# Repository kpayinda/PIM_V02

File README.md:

# PIM_V02
Flight-like design of PIM. After dev PIM_V01 was proven, this adds an FPGA and optimises size.

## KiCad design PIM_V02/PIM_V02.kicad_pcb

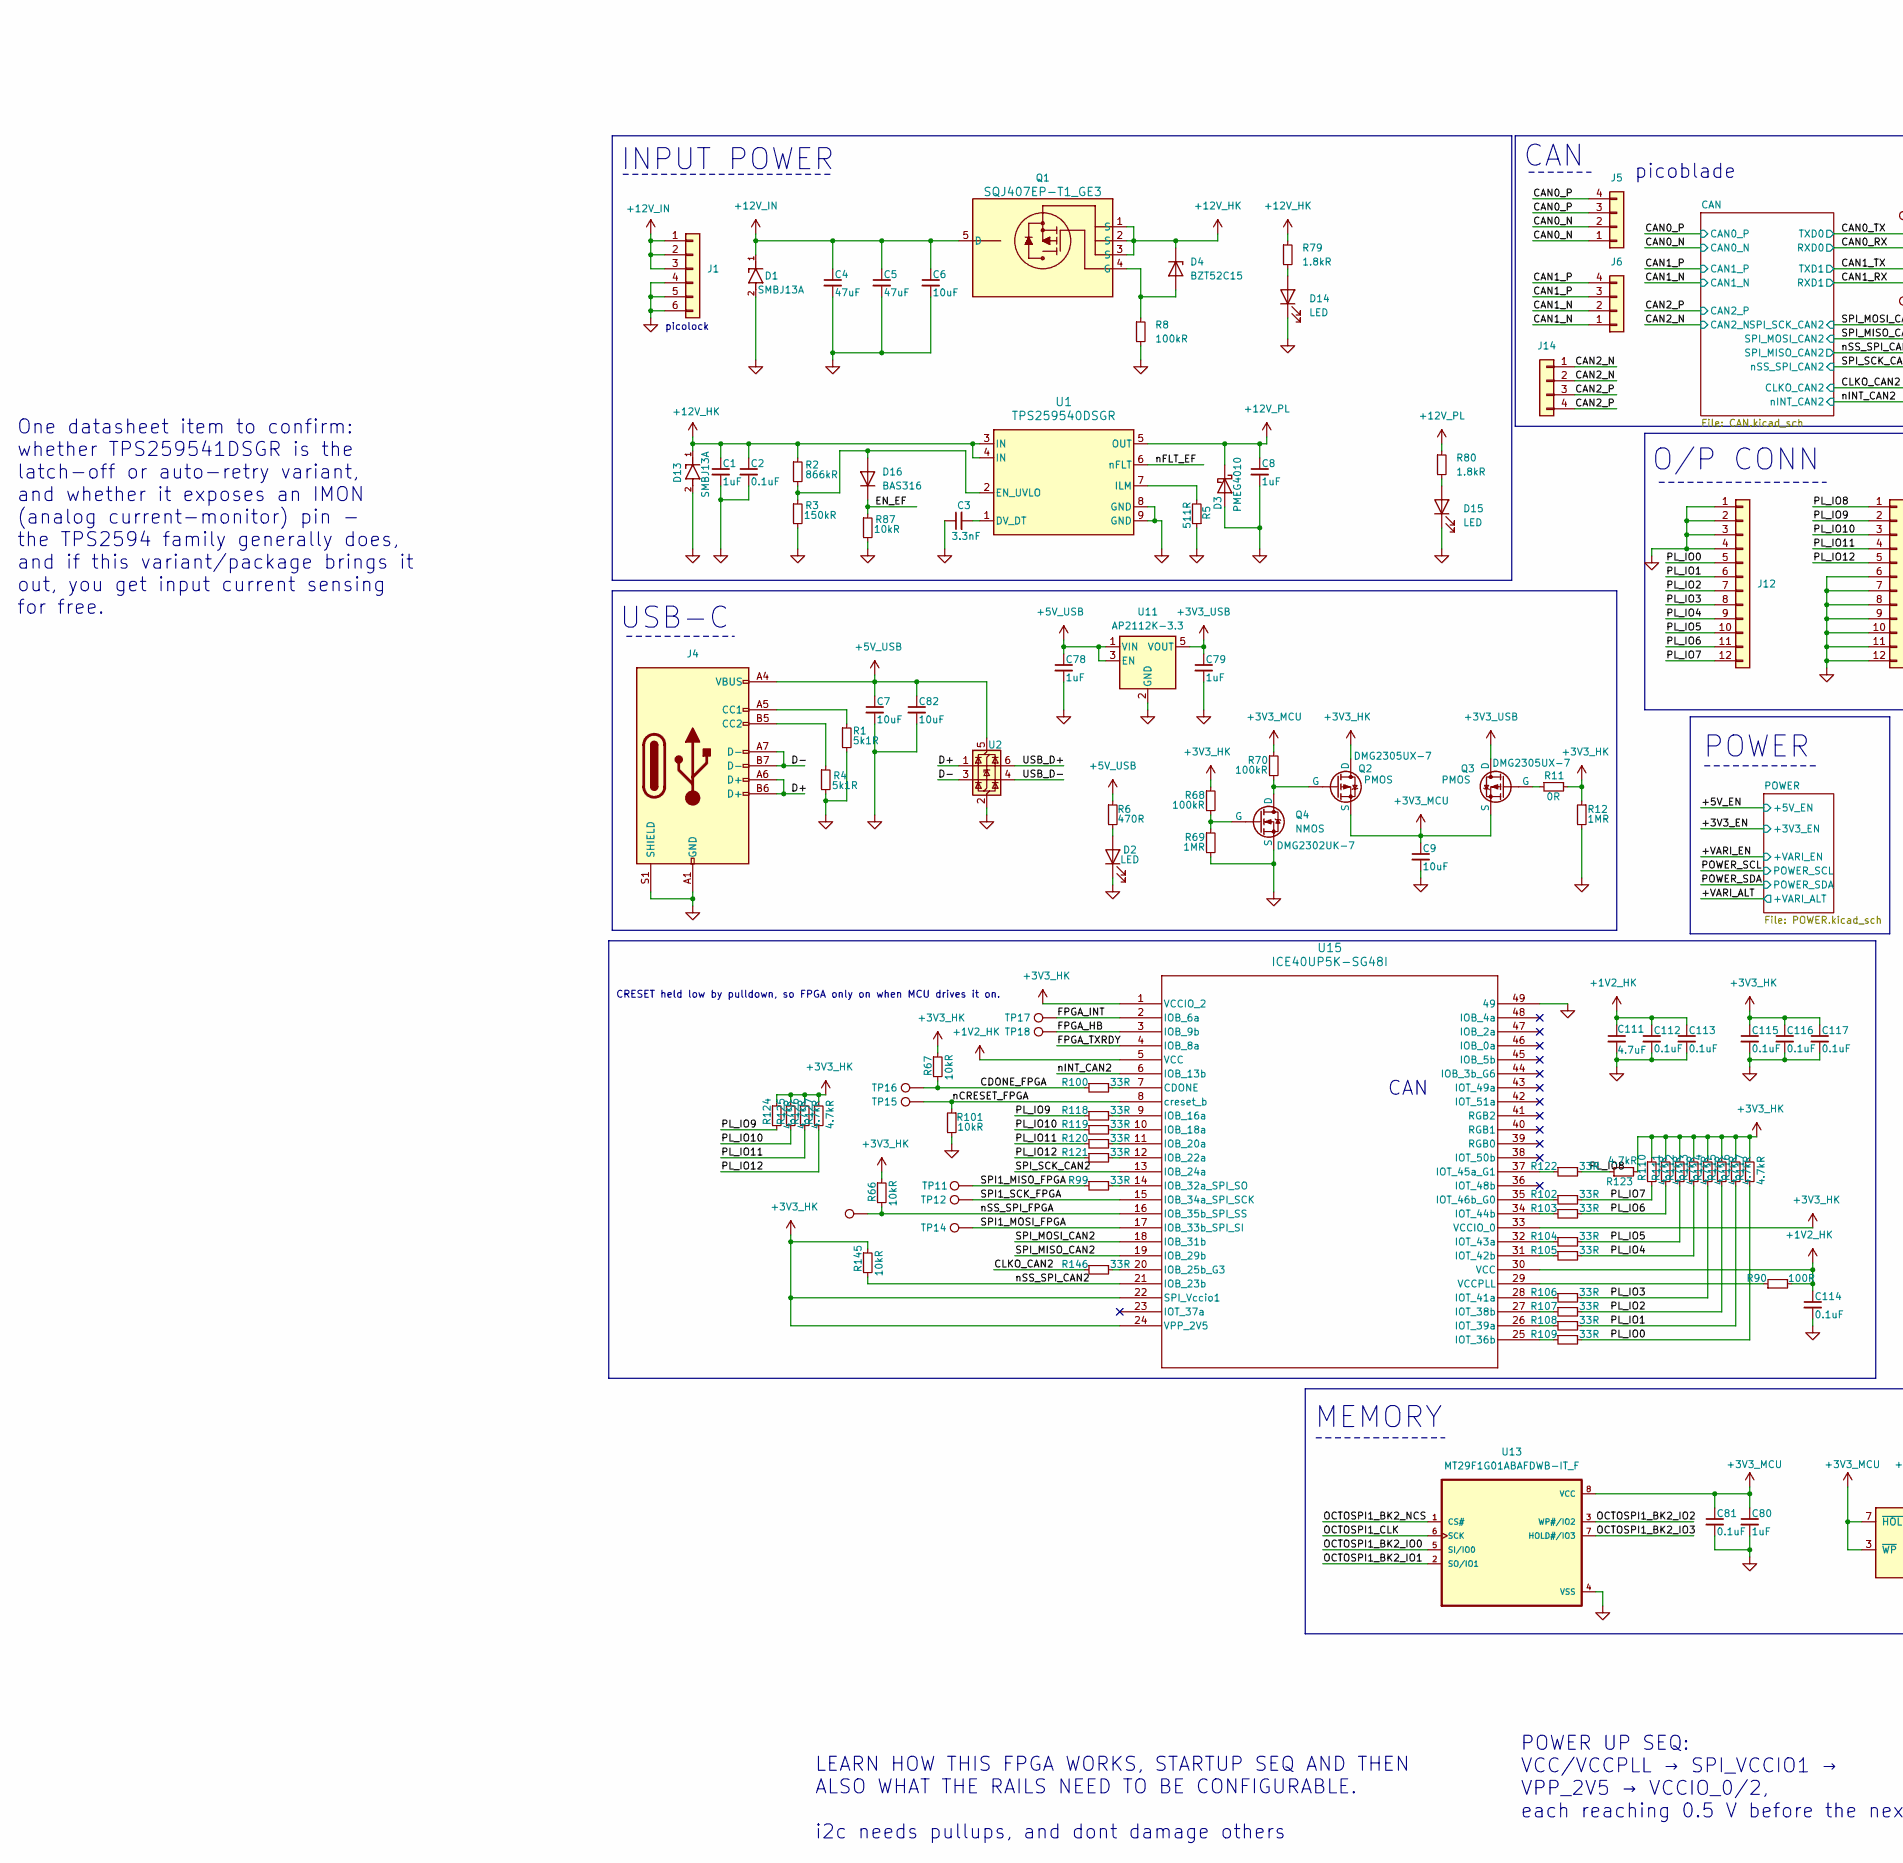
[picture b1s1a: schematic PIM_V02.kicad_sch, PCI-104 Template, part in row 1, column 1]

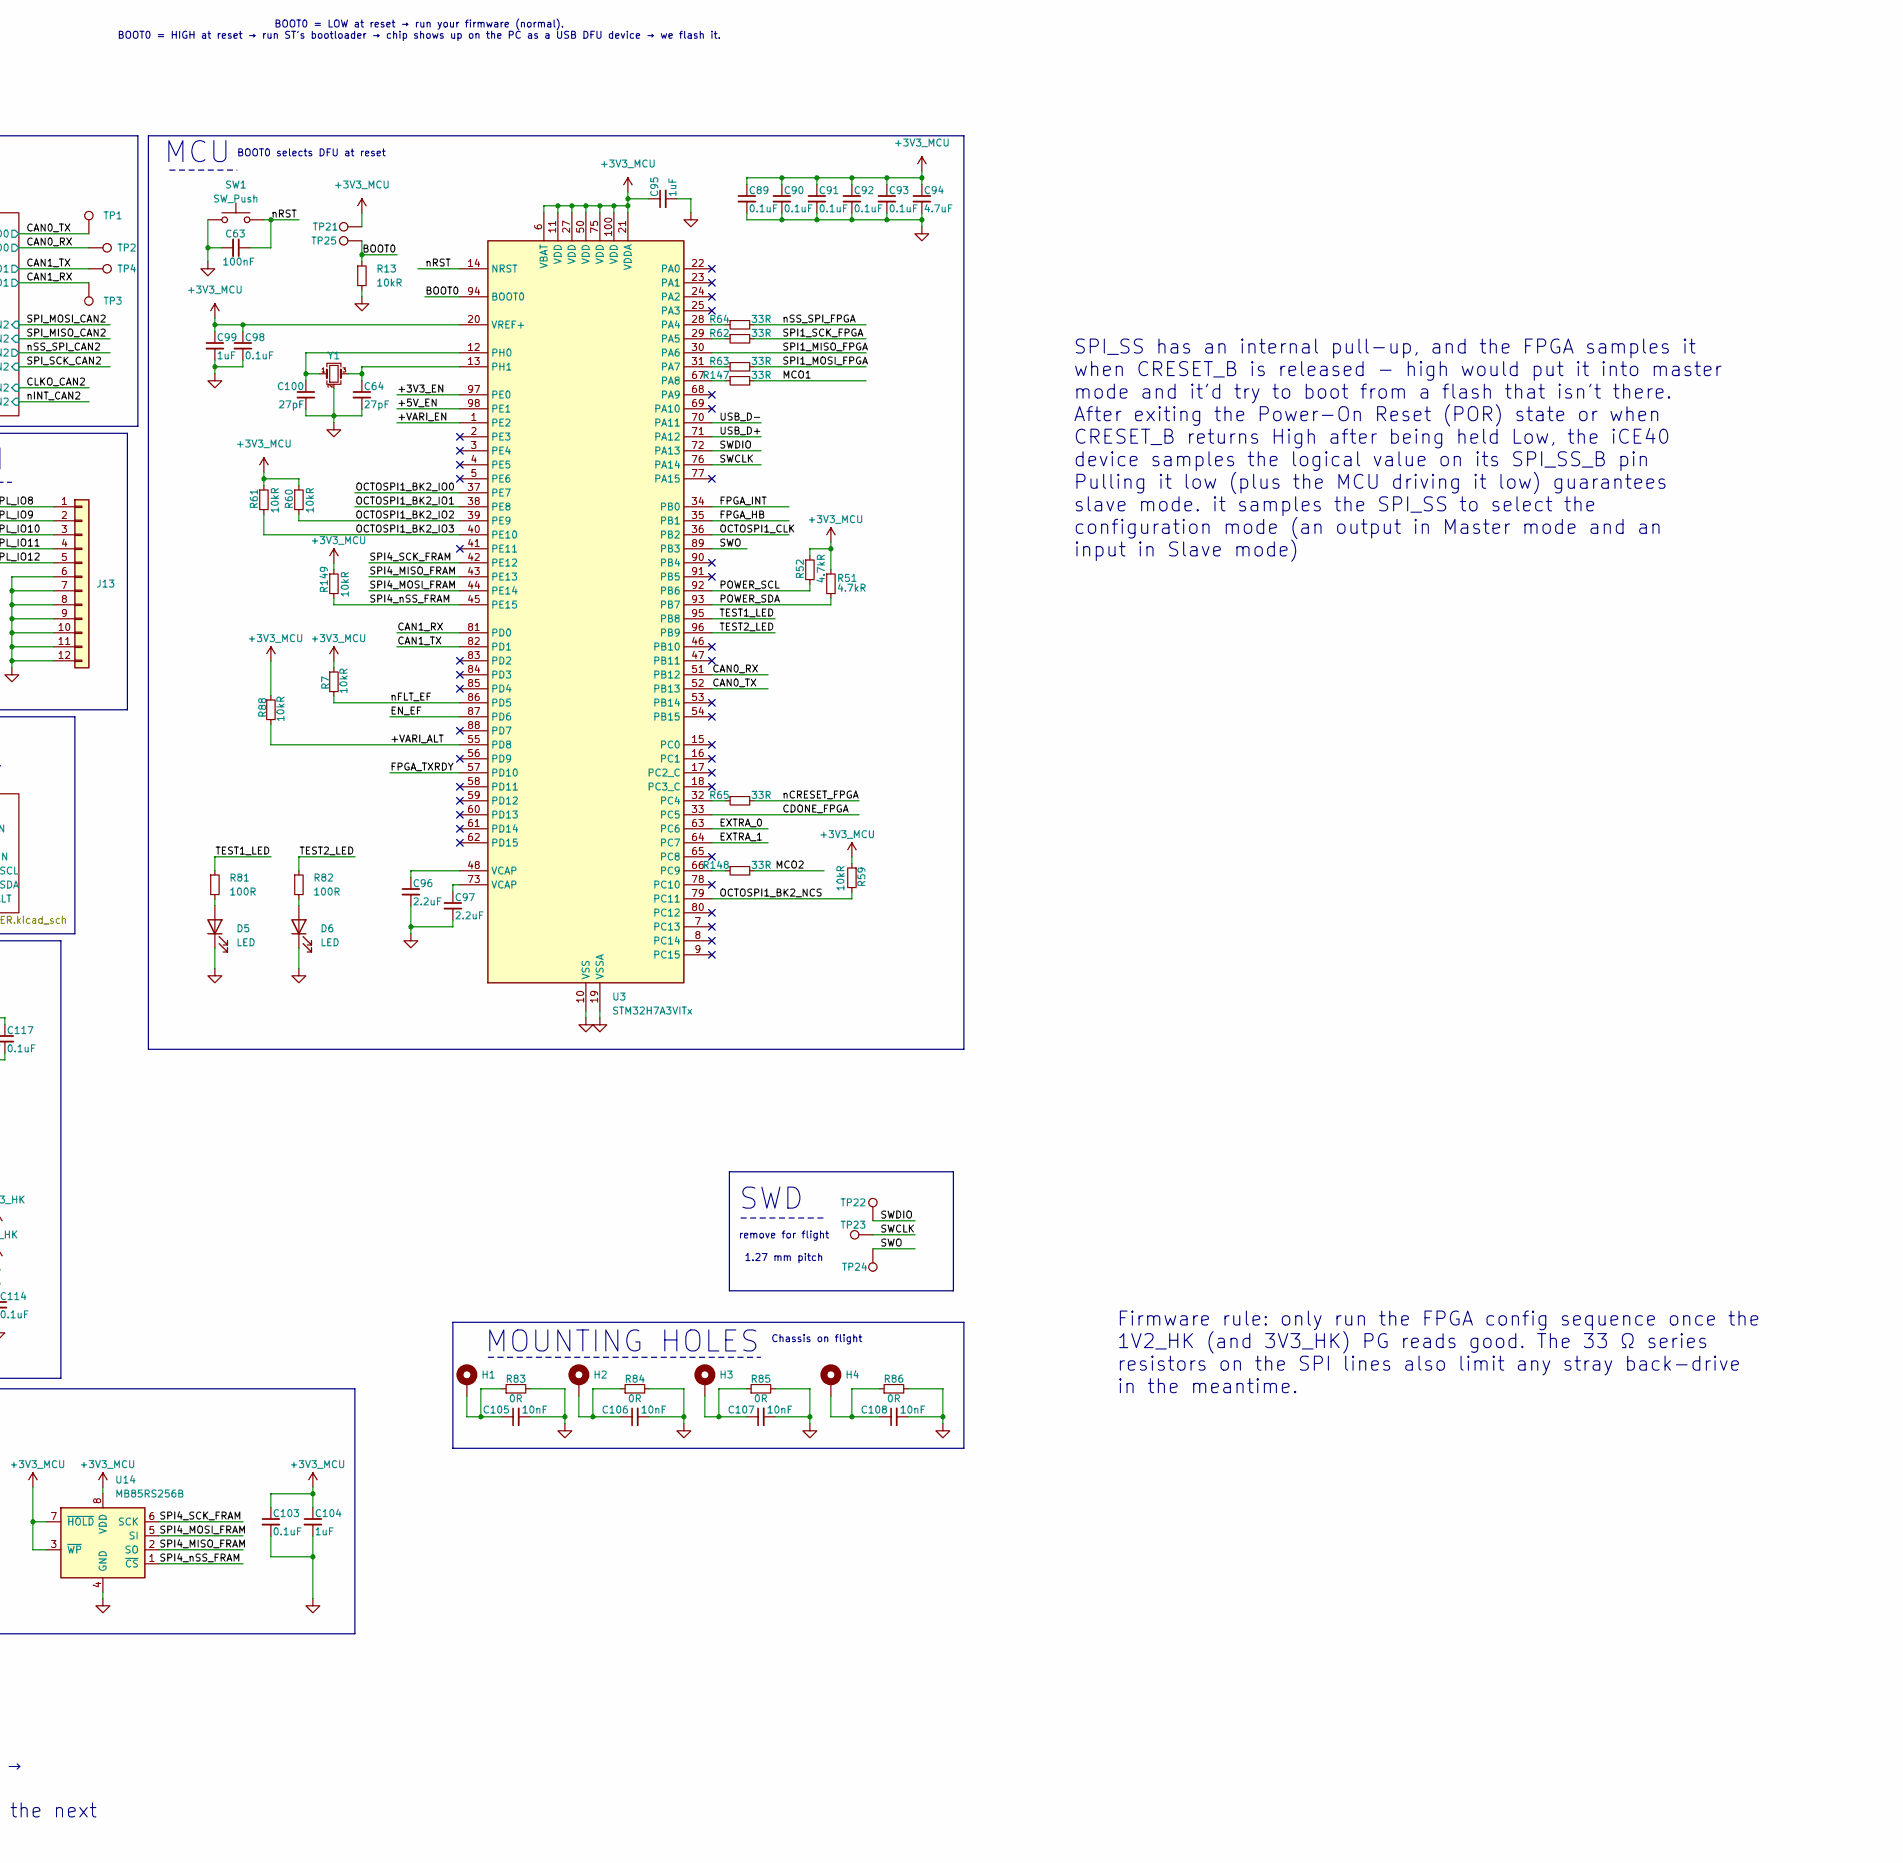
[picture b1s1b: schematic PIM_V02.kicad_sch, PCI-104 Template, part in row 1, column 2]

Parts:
C1, C8, C78, C79, C80, C95, C99, C104: 1uF; C_0603_1608Metric; MPN GCM188R71E105KA64J
C2, C81, C89, C90, C91, C92, C93, C98, C103, C112, C113, C114, C115, C116, C117: 0.1uF; C_0603_1608Metric; MPN GCM188R71H104KA57D
C3: 3.3nF; C_0603_1608Metric; MPN GCM1885C1H332JA16D
C4, C5: 47uF; C_1206_3216Metric; Rating 50V, MLCC; MPN GMC31X5R476M25NT
C6, C7, C9, C82: 10uF; C_0603_1608Metric; MPN GRT188R61E106ME13D
C63: 100nF; C_0603_1608Metric; MPN GCM188R71H104KA57D
C64, C100: 27pF; C_0603_1608Metric; MPN GCM1885C1H270JA16D
C94, C111: 4.7uF; C_0603_1608Metric; MPN MSAST168BB5475MTNA01
C96, C97: 2.2uF; C_0603_1608Metric; MPN GRT188R61E225ME13D
C105, C106, C107, C108: 10nF; C_0603_1608Metric; MPN GCM188R71H103KA37J
D1, D13: SMBJ13A
D2, D5, D6, D14, D15: LED; LED_0603_1608Metric; MPN 150060GS75000
D3: PMEG4010; Nexperia_CFP3_SOD-123W; MPN PMEG4010ER,115
D4: BZT52C15; Nexperia_CFP3_SOD-123W; MPN BZT52C15
D16: BAS316; D_SOD-323
H1, H2, H3, H4: MountingHole_Pad; MountingHole_2.2mm_M2_Pad
J1: Conn_01x06; Molex_Pico-Lock_504050-0691_1x06-1MP_P1.50mm_Horizontal; MPN 5040500691
J4: USB_C_Receptacle_USB2.0_14P; USB_C_Receptacle_GCT_USB4105-xx-A_16P_TopMnt_Horizontal; MPN USB4105-GF-A
J5, J6, J14: Conn_01x04; Molex_PicoBlade_53261-0471_1x04-1MP_P1.25mm_Horizontal; MPN 0532610471
J12, J13: Conn_01x12; 5040501291
Q1: SQJ407EP-T1_GE3; PowerPAK-SO-8L_Option-2_VIS; MPN SQJ407EP-T1_GE3
Q2, Q3: PMOS; SOT-23-3; MPN DMG2305UX-7
Q4: NMOS; SOT-23-3; MPN DMG2302UK-7
R1, R4: 5k1R; R_0603_1608Metric; MPN ERJ-3EKF5101V
R2: 866kR; R_0603_1608Metric; MPN ERJ-3EKF8663V
R3: 150kR; R_0603_1608Metric; MPN ERJ-3EKF1503V
R5: 511R; R_0603_1608Metric; MPN ERJ-3EKF5110V
R6: 470R; R_0603_1608Metric; MPN ERJ-3EKF4700V
R7, R13, R59, R60, R61, R66, R67, R88, R145, R149: 10kR; R_0603_1608Metric; MPN ERJ-3EKF1002V
R8, R68, R70: 100kR; R_0603_1608Metric; MPN ERJ-3EKF1003V
R11, R83, R84, R85, R86: 0R; R_0603_1608Metric; MPN ERJ-3GEY0R00V
R12, R69: 1MR; R_0603_1608Metric; MPN ERJ-3EKF1004V
R51, R52: 4.7kR; R_0603_1608Metric; MPN ERJ-3EKF4701V
R62, R63, R64, R65, R122, R147, R148: 33R; R_0603_1608Metric; MPN ERJ-3EKF33R0V
R79, R80: 1.8kR; R_0603_1608Metric; MPN ERJ-3EKF1801V
R81, R82, R90: 100R; R_0603_1608Metric; MPN ERJ-3EKF1000V
R87, R101: 10kR; R_0603_1608Metric
R99, R100, R102, R103, R104, R105, R106, R107, R108, R109, R118, R119, R120, R121, R146: 33R; R_0402_1005Metric; MPN ERJ-2RKF33R0X
R110, R111, R112, R113, R114, R115, R116, R117, R123, R124, R125, R126, R127: 4.7kR; R_0402_1005Metric; MPN ERJ-2RKF4701X
SW1: SW_Push; SW_SPST_B3U-1000P; MPN B3U-1000P
TP1, TP2, TP3, TP4, TP11, TP12, TP13, TP14, TP15, TP16, TP17, TP18, TP21, TP22, TP23, TP24, TP25: TestPoint; TestPoint_Pad_D1.0mm
U1: TPS259540DSGR; DSG0008A; MPN TPS259540DSGR
U2: USBLC6-2SC6; SOT-23-6; MPN USBLC6-2SC6
U3: STM32H7A3VITx; LQFP-100_14x14mm_P0.5mm; MPN STM32H7A3VIT6
U11: AP2112K-3.3; SOT-23-5; MPN AP2112K-3.3TRG1
U13: MT29F1G01ABAFDWB-IT_F; GD5F1GQ5UEYIGR; PARTREV LTR
U14: MB85RS256B; JEITA_SOIC-8_3.9x4.9mm_P1.27mm; MPN MB85RS256BPNF-G-AMERE2
U15: ICE40UP5K-SG48I; QFN48_L-ASC10_ICE40ULTRAPLUS_MACHXO2_LAT
Y1: Crystal_GND24_Small; Crystal_SMD_Abracon_ABM8G-4Pin_3.2x2.5mm; MPN ABM8G-24.000MHZ-18-D2Y-T3

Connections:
+1V2_HK: C111.1, C112.1, C113.1, C114.1, R90.2, U15.5 (VCC), U15.30 (VCC); also elsewhere on the board
+3V3_HK: C115.1, C116.1, C117.1, Q2.1 (D), R11.2, R12.1, R66.1, R67.1, R68.1, R110.1, R111.1, R112.1, R113.1, R114.1, R115.1, R116.1, R117.1, R123.2, R124.1, R125.1, R126.1, R127.1, R145.1, U15.1 (VCCIO_2), U15.22 (SPI_Vccio1), U15.24 (VPP_2V5), U15.33 (VCCIO_0); also elsewhere on the board
+3V3_MCU: C9.1, C80.1, C81.1, C89.1, C90.1, C91.1, C92.1, C93.1, C94.1, C95.1, C98.1, C99.1, C103.1, C104.1, Q2.3 (S), Q3.3 (S), R7.1, R51.1, R52.1, R59.1, R60.1, R61.1, R70.1, R88.1, R149.1, TP21.1, U3.6 (VBAT), U3.11 (VDD), U3.20 (VREF+), U3.21 (VDDA), U3.27 (VDD), U3.50 (VDD), U3.75 (VDD), U3.100 (VDD), U13.8 (VCC), U14.3 (~WP), U14.7 (~HOLD), U14.8 (VDD); also elsewhere on the board
+3V3_USB: C79.1, Q3.1 (D), U11.5 (VOUT)
+5V_USB: C7.1, C78.1, C82.1, J4.A4 (VBUS), J4.A9 (VBUS), J4.B4 (VBUS), J4.B9 (VBUS), R6.1, U2.5 (VBUS), U11.1 (VIN), U11.3 (EN)
+12V_HK: C1.1, C2.1, D4.1 (K), D13.1, Q1.1 (S), Q1.2 (S), Q1.3 (S), R2.1, R79.1, U1.3 (IN), U1.4 (IN); also elsewhere on the board
+12V_IN: C4.1, C5.1, C6.1, D1.1, J1.1, J1.2, J1.3, Q1.5 (D)
+12V_PL: C8.1, D3.1 (K), R80.1, U1.5 (OUT); also elsewhere on the board
/+3V3_EN: U3.97 (PE0); also elsewhere on the board
/+5V_EN: U3.98 (PE1); also elsewhere on the board
/+VARI_ALT: R88.2, U3.55 (PD8); also elsewhere on the board
/+VARI_EN: U3.1 (PE2); also elsewhere on the board
/BOOT0: R13.1, TP25.1, U3.94 (BOOT0)
/CAN0_N: J5.1, J5.2; also elsewhere on the board
/CAN0_P: J5.3, J5.4; also elsewhere on the board
/CAN0_RX: TP2.1, U3.51 (PB12); also elsewhere on the board
/CAN0_TX: TP1.1, U3.52 (PB13); also elsewhere on the board
/CAN1_N: J6.1, J6.2; also elsewhere on the board
/CAN1_P: J6.3, J6.4; also elsewhere on the board
/CAN1_RX: TP3.1, U3.81 (PD0); also elsewhere on the board
/CAN1_TX: TP4.1, U3.82 (PD1); also elsewhere on the board
/CAN2_N: J14.1, J14.2; also elsewhere on the board
/CAN2_P: J14.3, J14.4; also elsewhere on the board
/CDONE_FPGA: R67.2, R100.1, TP16.1, U3.33 (PC5)
/CLKO_CAN2: R146.1; also elsewhere on the board
/D+: J4.A6 (D+), J4.B6 (D+), U2.1 (I/O1)
/D-: J4.A7 (D-), J4.B7 (D-), U2.3 (I/O2)
/EN_EF: D16.1 (K), R87.1, U3.87 (PD6)
/EXTRA_0: U3.63 (PC6)
/EXTRA_1: U3.64 (PC7)
/FPGA_HB: TP18.1, U3.35 (PB1), U15.3 (IOB_9b)
/FPGA_INT: TP17.1, U3.34 (PB0), U15.2 (IOB_6a)
/FPGA_TXRDY: U3.57 (PD10), U15.4 (IOB_8a)
/MCO1: R147.2
/MCO2: R148.2
/OCTOSPI1_BK2_IO0: U3.37 (PE7), U13.5 (SI/IO0)
/OCTOSPI1_BK2_IO1: U3.38 (PE8), U13.2 (SO/IO1)
/OCTOSPI1_BK2_IO2: R60.2, U3.39 (PE9), U13.3 (WP#/IO2)
/OCTOSPI1_BK2_IO3: R61.2, U3.40 (PE10), U13.7 (HOLD#/IO3)
/OCTOSPI1_BK2_NCS: R59.2, U3.79 (PC11), U13.1 (CS#)
/OCTOSPI1_CLK: U3.36 (PB2), U13.6 (SCK)
/PL_IO0: J12.5, R109.2, R117.2
/PL_IO1: J12.6, R108.2, R116.2
/PL_IO2: J12.7, R107.2, R115.2
/PL_IO3: J12.8, R106.2, R114.2
/PL_IO4: J12.9, R105.2, R113.2
/PL_IO5: J12.10, R104.2, R112.2
/PL_IO6: J12.11, R103.2, R111.2
/PL_IO7: J12.12, R102.2, R110.2
/PL_IO8: J13.1, R122.2, R123.1
/PL_IO9: J13.2, R118.1, R124.2
/PL_IO10: J13.3, R119.1, R125.2
/PL_IO11: J13.4, R120.1, R126.2
/PL_IO12: J13.5, R121.1, R127.2
/POWER_SCL: R52.2, U3.92 (PB6); also elsewhere on the board
/POWER_SDA: R51.2, U3.93 (PB7); also elsewhere on the board
/SPI1_MISO_FPGA: R99.1, TP11.1, U3.30 (PA6)
/SPI1_MOSI_FPGA: R63.2, TP14.1, U15.17 (IOB_33b_SPI_SI)
/SPI1_SCK_FPGA: R62.2, TP12.1, U15.15 (IOB_34a_SPI_SCK)
/SPI4_MISO_FRAM: U3.43 (PE13), U14.2 (SO)
/SPI4_MOSI_FRAM: U3.44 (PE14), U14.5 (SI)
/SPI4_SCK_FRAM: U3.42 (PE12), U14.6 (SCK)
/SPI4_nSS_FRAM: R149.2, U3.45 (PE15), U14.1 (~CS)
/SPI_MISO_CAN2: U15.19 (IOB_29b); also elsewhere on the board
/SPI_MOSI_CAN2: U15.18 (IOB_31b); also elsewhere on the board
/SPI_SCK_CAN2: U15.13 (IOB_24a); also elsewhere on the board
/SWCLK: TP23.1, U3.76 (PA14)
/SWDIO: TP22.1, U3.72 (PA13)
/SWO: TP24.1, U3.89 (PB3)
/TEST1_LED: R81.1, U3.95 (PB8)
/TEST2_LED: R82.1, U3.96 (PB9)
/USB_D+: U2.6 (I/O1), U3.71 (PA12)
/USB_D-: U2.4 (I/O2), U3.70 (PA11)
/nCRESET_FPGA: R65.2, R101.1, TP15.1, U15.8 (creset_b)
/nFLT_EF: R7.2, U1.6 (nFLT), U3.86 (PD5)
/nINT_CAN2: U15.6 (IOB_13b); also elsewhere on the board
/nRST: C63.1, SW1.2, U3.14 (NRST)
/nSS_SPI_CAN2: R145.2, U15.21 (IOB_23b); also elsewhere on the board
/nSS_SPI_FPGA: R64.2, R66.2, TP13.1, U15.16 (IOB_35b_SPI_SS)
GND: C1.2, C2.2, C3.1, C4.2, C5.2, C6.2, C7.2, C8.2, C9.2, C63.2, C64.2, C78.2, C79.2, C80.2, C81.2, C82.2, C89.2, C90.2, C91.2, C92.2, C93.2, C94.2, C95.2, C96.2, C97.2, C98.2, C99.2, C100.2, C103.2, C104.2, C105.2, C106.2, C107.2, C108.2, C111.2, C112.2, C113.2, C114.2, C115.2, C116.2, C117.2, D1.2, D2.1 (K), D3.2 (A), D5.1 (K), D6.1 (K), D13.2, D14.1 (K), D15.1 (K), J1.4, J1.5, J1.6, J4.A1 (GND), J4.A12 (GND), J4.B1 (GND), J4.B12 (GND), J4.S1 (SHIELD), J12.1, J12.2, J12.3, J12.4, J13.6, J13.7, J13.8, J13.9, J13.10, J13.11, J13.12, Q4.3 (S), R1.2, R3.2, R4.2, R5.1, R8.2, R12.2, R13.2, R69.2, R83.2, R84.2, R85.2, R86.2, R87.2, R101.2, SW1.1, U1.8 (GND), U1.9 (GND), U2.2 (GND), U3.10 (VSS), U3.19 (VSSA), U3.26 (VSS), U3.49 (VSS), U3.74 (VSS), U3.99 (VSS), U11.2 (GND), U13.4 (VSS), U14.4 (GND), U15.49, Y1.2 (G), Y1.4 (G); also elsewhere on the board
unnamed: C96.1, U3.48 (VCAP)
unnamed: C97.1, U3.73 (VCAP)
unnamed: C105.1, H1.1, R83.1
unnamed: C106.1, H2.1, R84.1
unnamed: C107.1, H3.1, R85.1
unnamed: C108.1, H4.1, R86.1
unnamed: D2.2 (A), R6.2
unnamed: D4.2 (A), Q1.4 (G), R8.1
unnamed: D5.2 (A), R81.2
unnamed: D6.2 (A), R82.2
unnamed: D14.2 (A), R79.2
unnamed: D15.2 (A), R80.2
unnamed: D16.2 (A), R2.2, R3.1, U1.2 (EN_UVLO)
unnamed: J4.A5 (CC1), R1.1
unnamed: J4.B5 (CC2), R4.1
unnamed: Q2.2 (G), Q4.1 (D), R70.2
unnamed: Q3.2 (G), R11.1
unnamed: Q4.2 (G), R68.2, R69.1
unnamed: C3.2, U1.1 (DV_DT)
unnamed: R5.2, U1.7 (ILM)
unnamed: R64.1, U3.28 (PA4)
unnamed: R62.1, U3.29 (PA5)
unnamed: R63.1, U3.31 (PA7)
unnamed: R147.1, U3.67 (PA8)
unnamed: R65.1, U3.32 (PC4)
unnamed: R148.1, U3.66 (PC9)
unnamed: C100.1, U3.12 (PH0), Y1.1
unnamed: C64.1, U3.13 (PH1), Y1.3
unnamed: R100.2, U15.7 (CDONE)
unnamed: R118.2, U15.9 (IOB_16a)
unnamed: R119.2, U15.10 (IOB_18a)
unnamed: R120.2, U15.11 (IOB_20a)
unnamed: R121.2, U15.12 (IOB_22a)
unnamed: R146.2, U15.20 (IOB_25b_G3)
unnamed: R99.2, U15.14 (IOB_32a_SPI_SO)
unnamed: R109.1, U15.25 (IOT_36b)
unnamed: R107.1, U15.27 (IOT_38b)
unnamed: R108.1, U15.26 (IOT_39a)
unnamed: R106.1, U15.28 (IOT_41a)
unnamed: R105.1, U15.31 (IOT_42b)
unnamed: R104.1, U15.32 (IOT_43a)
unnamed: R103.1, U15.34 (IOT_44b)
unnamed: R122.1, U15.37 (IOT_45a_G1)
unnamed: R102.1, U15.35 (IOT_46b_G0)
unnamed: R90.1, U15.29 (VCCPLL)

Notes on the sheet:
BOOT0 selects DFU at reset
LEARN HOW THIS FPGA WORKS, STARTUP SEQ AND THEN ALSO WHAT THE RAILS NEED TO BE CONFIGURABLE. i2c needs pullups, and dont damage others
picoblade
POWER UP SEQ: VCC/VCCPLL → SPI_VCCIO1 → VPP_2V5 → VCCIO_0/2, each reaching 0.5 V before the next
BOOT0 = LOW at reset → run your firmware (normal). BOOT0 = HIGH at reset → run ST's bootloader → chip shows up on the PC as a USB DFU device → we flash it.
remove for flight 1.27 mm pitch
SPI_SS has an internal pull-up, and the FPGA samples it when CRESET_B is released - high would put it into master mode and it'd try to boot from a flash that isn't there. After exiting the Power-On Reset (POR) state or when CRESET_B returns High after being held Low, the iCE40 device samples the lo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
CRESET held low by pulldown, so FPGA only on when MCU drives it on.
USB-C
Chassis on flight
POWER
MCU
One datasheet item to confirm: whether TPS259541DSGR is the latch-off or auto-retry variant, and whether it exposes an IMON (analog current-monitor) pin - the TPS2594 family generally does, and if this variant/package brings it out, you get input current sensing for free.
picolock
O/P CONN
Firmware rule: only run the FPGA config sequence once the 1V2_HK (and 3V3_HK) PG reads good. The 33 Ω series resistors on the SPI lines also limit any stray back-drive in the meantime.
INPUT POWER
CAN
MEMORY
MOUNTING HOLES
SWD

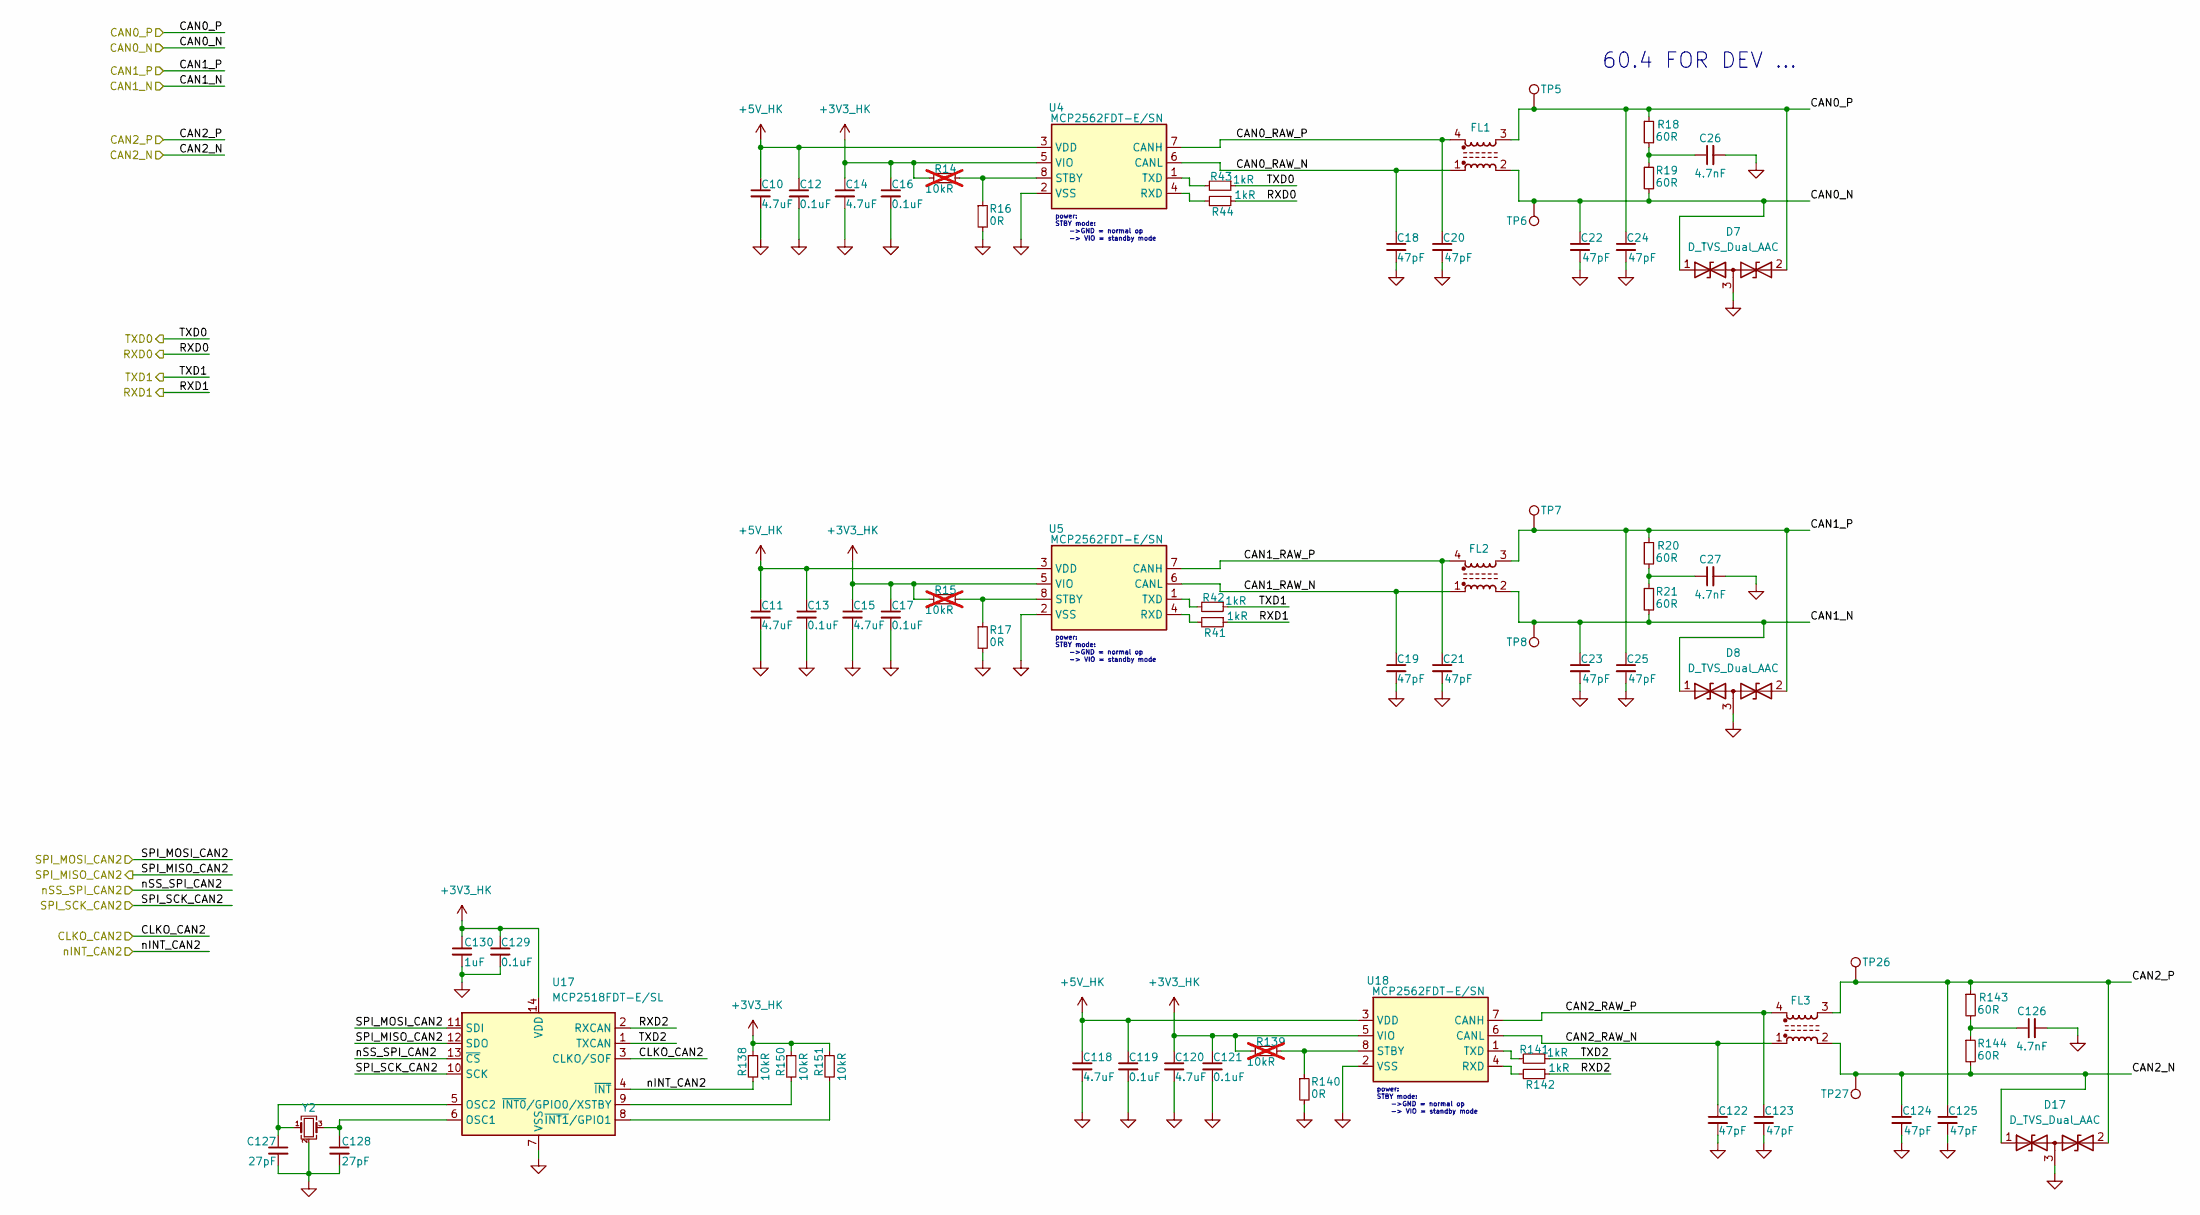
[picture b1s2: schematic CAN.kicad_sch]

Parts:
C10, C11, C14, C15, C118, C120: 4.7uF; C_0603_1608Metric; MPN MSAST168BB5475MTNA01
C12, C13, C16, C17, C119, C121, C129: 0.1uF; C_0603_1608Metric; MPN GCM188R71H104KA57D
C18, C19, C20, C21, C22, C23, C24, C25, C122, C123, C124, C125: 47pF; C_0603_1608Metric; MPN GCM1885C1H470JA16D
C26, C27, C126: 4.7nF; C_0603_1608Metric; MPN GCM1885C1H472GA16D
C127, C128: 27pF; C_0603_1608Metric; MPN GCM1885C1H270JA16D
C130: 1uF; C_0603_1608Metric; MPN GCM188R71E105KA64J
D7, D8, D17: D_TVS_Dual_AAC; SOT-23-3; MPN ESD16VHYFHT116
FL1, FL2, FL3: Choke_CommonMode_FerriteCore_1243; L_CommonModeChoke_Coilcraft_1812CAN; MPN ACT45B-101-2P-TL003
R14, R15, R139: 10kR; R_0603_1608Metric; MPN ERJ-3EKF1002V; not fitted
R16, R17, R140: 0R; R_0603_1608Metric; MPN ERJ-3GEY0R00V
R18, R19, R20, R21, R143, R144: 60R; R_0603_1608Metric; MPN ERJ-3EKF60R4V
R41, R42, R43, R44, R141, R142: 1kR; R_0603_1608Metric; MPN ERJ-3EKF1001V
R138, R150, R151: 10kR; R_0603_1608Metric; MPN ERJ-3EKF1002V
TP5, TP6, TP7, TP8, TP26, TP27: TestPoint; TestPoint_Pad_D1.0mm
U4, U5, U18: MCP2562FDT-E/SN; SOIC-8_3.9x4.9mm_P1.27mm; MPN MCP2562FDT-E/SN
U17: MCP2518FDT-E/SL; SOIC-14_3.9x8.7mm_P1.27mm
Y2: Crystal_GND24_Small; Crystal_SMD_Abracon_ABM8G-4Pin_3.2x2.5mm; MPN ABM8G-40.000MHZ-18-D2Y-T

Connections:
+3V3_HK: C14.1, C15.1, C16.1, C17.1, C120.1, C121.1, C129.1, C130.1, R14.2, R15.2, R138.1, R139.2, R150.1, R151.1, U4.5 (VIO), U5.5 (VIO), U17.14 (VDD), U18.5 (VIO); also elsewhere on the board
+5V_HK: C10.1, C11.1, C12.1, C13.1, C118.1, C119.1, U4.3 (VDD), U5.3 (VDD), U18.3 (VDD); also elsewhere on the board
/CAN0_N: C22.1, D7.1 (A1), FL1.2, R19.2, TP6.1; also elsewhere on the board
/CAN0_P: C24.1, D7.2 (A2), FL1.3, R18.1, TP5.1; also elsewhere on the board
/CAN0_RX: R44.1; also elsewhere on the board
/CAN0_TX: R43.1; also elsewhere on the board
/CAN1_N: C23.1, D8.1 (A1), FL2.2, R21.2, TP8.1; also elsewhere on the board
/CAN1_P: C25.1, D8.2 (A2), FL2.3, R20.1, TP7.1; also elsewhere on the board
/CAN1_RX: R41.1; also elsewhere on the board
/CAN1_TX: R42.1; also elsewhere on the board
/CAN2_N: C124.1, D17.1 (A1), FL3.2, R144.2, TP27.1; also elsewhere on the board
/CAN2_P: C125.1, D17.2 (A2), FL3.3, R143.1, TP26.1; also elsewhere on the board
/CAN/CAN0_RAW_N: C18.1, FL1.1, U4.6 (CANL)
/CAN/CAN0_RAW_P: C20.1, FL1.4, U4.7 (CANH)
/CAN/CAN1_RAW_N: C19.1, FL2.1, U5.6 (CANL)
/CAN/CAN1_RAW_P: C21.1, FL2.4, U5.7 (CANH)
/CAN/CAN2_RAW_N: C122.1, FL3.1, U18.6 (CANL)
/CAN/CAN2_RAW_P: C123.1, FL3.4, U18.7 (CANH)
/CAN/RXD2: R142.1, U17.2 (RXCAN)
/CAN/TXD2: R141.1, U17.1 (TXCAN)
/CLKO_CAN2: U17.3 (CLKO/SOF); also elsewhere on the board
/SPI_MISO_CAN2: U17.11 (SDI); also elsewhere on the board
/SPI_MOSI_CAN2: U17.10 (SCK); also elsewhere on the board
/SPI_SCK_CAN2: U17.13 (~CS); also elsewhere on the board
/nINT_CAN2: R138.2, U17.4 (~INT); also elsewhere on the board
/nSS_SPI_CAN2: U17.12 (SDO); also elsewhere on the board
GND: C10.2, C11.2, C12.2, C13.2, C14.2, C15.2, C16.2, C17.2, C18.2, C19.2, C20.2, C21.2, C22.2, C23.2, C24.2, C25.2, C26.2, C27.2, C118.2, C119.2, C120.2, C121.2, C122.2, C123.2, C124.2, C125.2, C126.2, C127.2, C128.2, C129.2, C130.2, D7.3 (common), D8.3 (common), D17.3 (common), R16.2, R17.2, R140.2, U4.2 (VSS), U5.2 (VSS), U17.7 (VSS), U17.15 (VSS), U18.2 (VSS), Y2.2 (G), Y2.4 (G); also elsewhere on the board
unnamed: C26.1, R18.2, R19.1
unnamed: C27.1, R20.2, R21.1
unnamed: C126.1, R143.2, R144.1
unnamed: R44.2, U4.4 (RXD)
unnamed: R14.1, R16.1, U4.8 (STBY)
unnamed: R43.2, U4.1 (TXD)
unnamed: R41.2, U5.4 (RXD)
unnamed: R15.1, R17.1, U5.8 (STBY)
unnamed: R42.2, U5.1 (TXD)
unnamed: C128.1, U17.6 (OSC1), Y2.3
unnamed: C127.1, U17.5 (OSC2), Y2.1
unnamed: R150.2, U17.9 (~INT0/GPIO0/XSTBY)
unnamed: R151.2, U17.8 (~INT1/GPIO1)
unnamed: R142.2, U18.4 (RXD)
unnamed: R139.1, R140.1, U18.8 (STBY)
unnamed: R141.2, U18.1 (TXD)

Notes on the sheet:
60.4 FOR DEV ...
power: STBY mode: ->GND = normal op -> VIO = standby mode
